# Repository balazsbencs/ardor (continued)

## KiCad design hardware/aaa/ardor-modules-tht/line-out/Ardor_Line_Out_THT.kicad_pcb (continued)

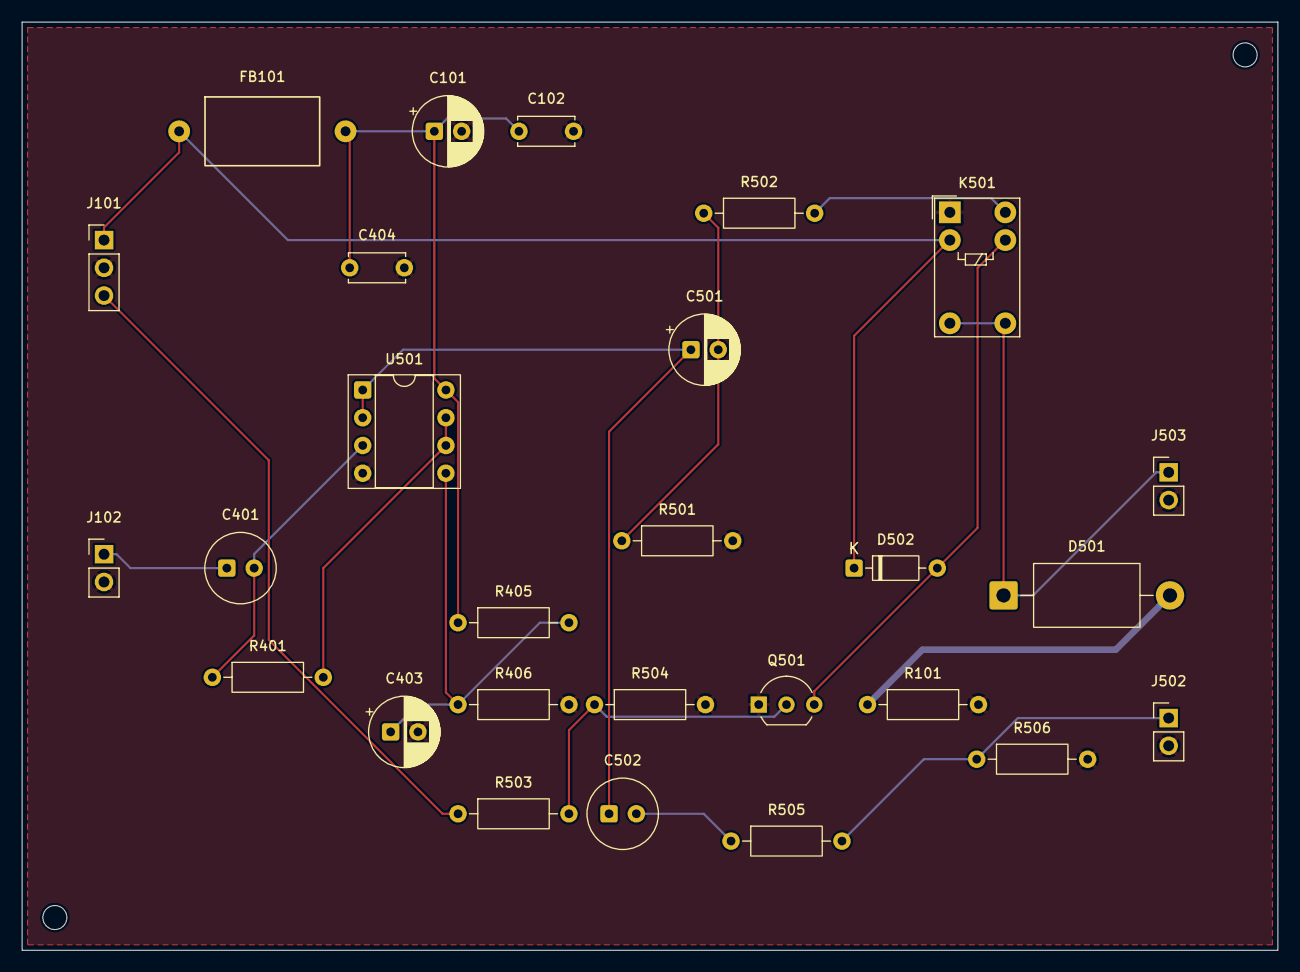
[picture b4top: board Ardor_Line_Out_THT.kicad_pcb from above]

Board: 2 copper layers, 115.0 x 85.0 mm, 29 parts (0 on the bottom side), 17 nets.

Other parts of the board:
H1, H2: MountingHole_2.2mm_M2

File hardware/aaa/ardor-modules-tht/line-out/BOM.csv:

Reference,Value,Footprint,Purchasing specification,Assembly
J102,MONO AUDIO INPUT FROM SOURCE,Connector_PinHeader_2.54mm:PinHeader_1x02_P2.54mm_Vertical,PinHeader_1x02_P2.54mm_Vertical,THT manual
J101,5V POWER + ENABLE INPUT,Connector_PinHeader_2.54mm:PinHeader_1x03_P2.54mm_Vertical,PinHeader_1x03_P2.54mm_Vertical,THT manual
J503,LINE AUDIO OUTPUT TO TS SOCKET,Connector_PinHeader_2.54mm:PinHeader_1x02_P2.54mm_Vertical,PinHeader_1x02_P2.54mm_Vertical,THT manual
J502,AUDIO OUTPUT TO AMP INPUT,Connector_PinHeader_2.54mm:PinHeader_1x02_P2.54mm_Vertical,PinHeader_1x02_P2.54mm_Vertical,THT manual
FB101,800R@100MHz / WE 7427501,Ardor_THT:Ferrite_WE_7427501_P15.24mm,Wurth Elektronik 7427501,THT manual
C101,22u / 25V polarized,Capacitor_THT:CP_Radial_D6.3mm_P2.50mm,"Radial electrolytic 22uF 25V, D<=6.3mm P2.5mm",THT manual
C102,100n / 50V X7R,Capacitor_THT:C_Disc_D5.0mm_W2.5mm_P5.00mm,"100nF 50V X7R radial, 5mm lead pitch",THT manual
C401,10u / 25V BIPOLAR,Ardor_THT:CP_Bipolar_D6.3mm_P2.50mm,Nichicon UES1E100MDM,THT manual
R401,100kR / 1% 0.25W,Resistor_THT:R_Axial_DIN0207_L6.3mm_D2.5mm_P10.16mm_Horizontal,Axial metal film 100kΩ 1% 0.25W,THT manual
U501,MCP6022-I/P,Package_DIP:DIP-8_W7.62mm_Socket,Microchip MCP6022-I/P,THT manual
C501,47u / 25V polarized,Capacitor_THT:CP_Radial_D6.3mm_P2.50mm,"Radial electrolytic 47uF 25V, D<=6.3mm P2.5mm",THT manual
R501,10kR / 1% 0.25W,Resistor_THT:R_Axial_DIN0207_L6.3mm_D2.5mm_P10.16mm_Horizontal,Axial metal film 10kΩ 1% 0.25W,THT manual
R502,100R / 1% 0.25W,Resistor_THT:R_Axial_DIN0207_L6.3mm_D2.5mm_P10.16mm_Horizontal,Axial metal film 100Ω 1% 0.25W,THT manual
K501,Omron G5V-1 DC5,Relay_THT:Relay_SPDT_Omron_G5V-1,Omron G5V-1 DC5,THT manual
D501,SA5.0CA-E3/54,Diode_THT:D_DO-15_P10.16mm_Horizontal,Vishay SA5.0CA-E3/54,THT manual
R101,0R / 1% 0.25W,Resistor_THT:R_Axial_DIN0207_L6.3mm_D2.5mm_P10.16mm_Horizontal,Axial metal film 0Ω 1% 0.25W,THT manual
Q501,2N3904 / E-B-C,Package_TO_SOT_THT:TO-92_Inline_Wide,onsemi 2N3904BU,THT manual
R503,470R / 1% 0.25W,Resistor_THT:R_Axial_DIN0207_L6.3mm_D2.5mm_P10.16mm_Horizontal,Axial metal film 470Ω 1% 0.25W,THT manual
R504,100kR / 1% 0.25W,Resistor_THT:R_Axial_DIN0207_L6.3mm_D2.5mm_P10.16mm_Horizontal,Axial metal film 100kΩ 1% 0.25W,THT manual
D502,1N4148,Diode_THT:D_DO-35_SOD27_P7.62mm_Horizontal,Vishay 1N4148-TAP,THT manual
R405,10kR / 1% 0.25W,Resistor_THT:R_Axial_DIN0207_L6.3mm_D2.5mm_P10.16mm_Horizontal,Axial metal film 10kΩ 1% 0.25W,THT manual
R406,10kR / 1% 0.25W,Resistor_THT:R_Axial_DIN0207_L6.3mm_D2.5mm_P10.16mm_Horizontal,Axial metal film 10kΩ 1% 0.25W,THT manual
C403,10u / 25V polarized,Capacitor_THT:CP_Radial_D6.3mm_P2.50mm,"Radial electrolytic 10uF 25V, D<=6.3mm P2.5mm",THT manual
C404,100n / 50V X7R,Capacitor_THT:C_Disc_D5.0mm_W2.5mm_P5.00mm,"100nF 50V X7R radial, 5mm lead pitch",THT manual
C502,10u / 25V BIPOLAR,Ardor_THT:CP_Bipolar_D6.3mm_P2.50mm,Nichicon UES1E100MDM,THT manual
R505,1kR / 1% 0.25W,Resistor_THT:R_Axial_DIN0207_L6.3mm_D2.5mm_P10.16mm_Horizontal,Axial metal film 1kΩ 1% 0.25W,THT manual
R506,100kR / 1% 0.25W,Resistor_THT:R_Axial_DIN0207_L6.3mm_D2.5mm_P10.16mm_Horizontal,Axial metal film 100kΩ 1% 0.25W,THT manual

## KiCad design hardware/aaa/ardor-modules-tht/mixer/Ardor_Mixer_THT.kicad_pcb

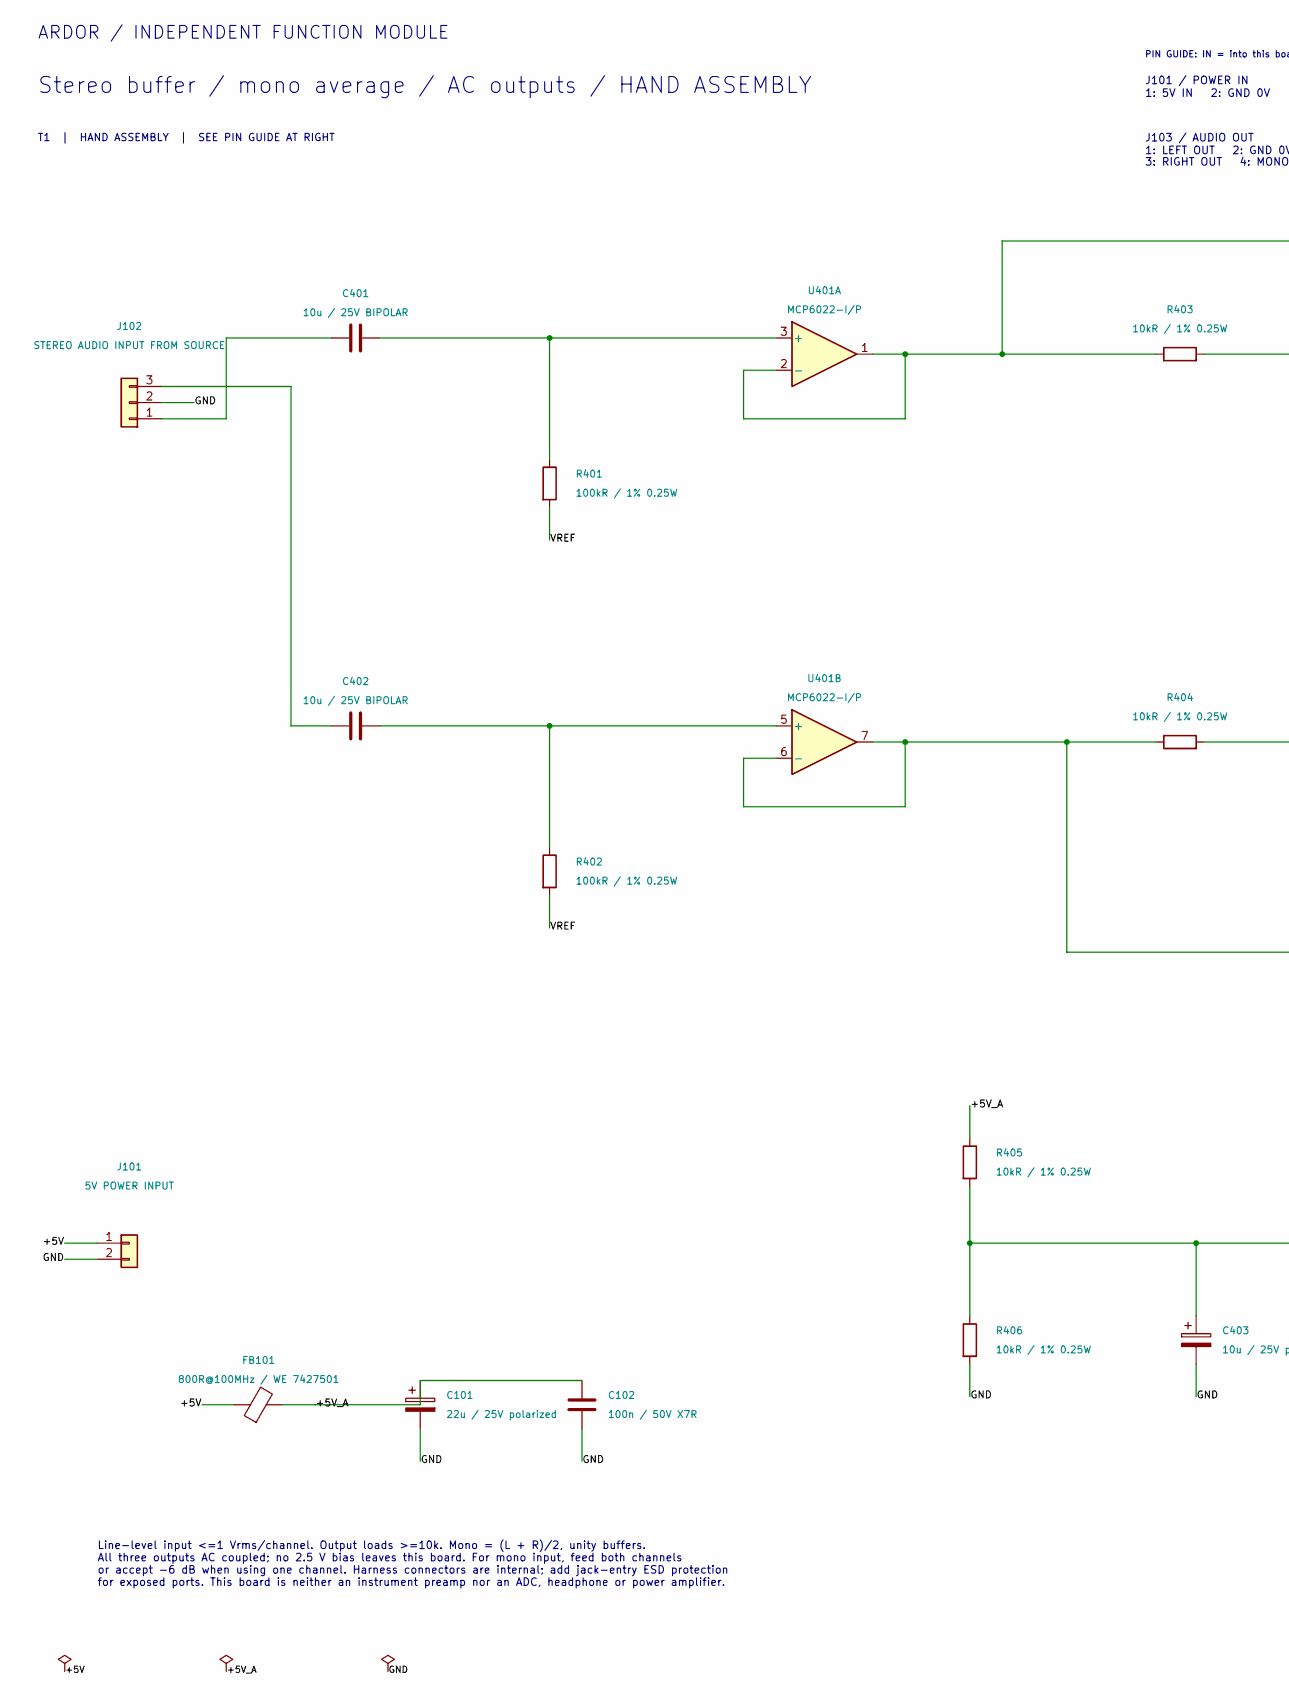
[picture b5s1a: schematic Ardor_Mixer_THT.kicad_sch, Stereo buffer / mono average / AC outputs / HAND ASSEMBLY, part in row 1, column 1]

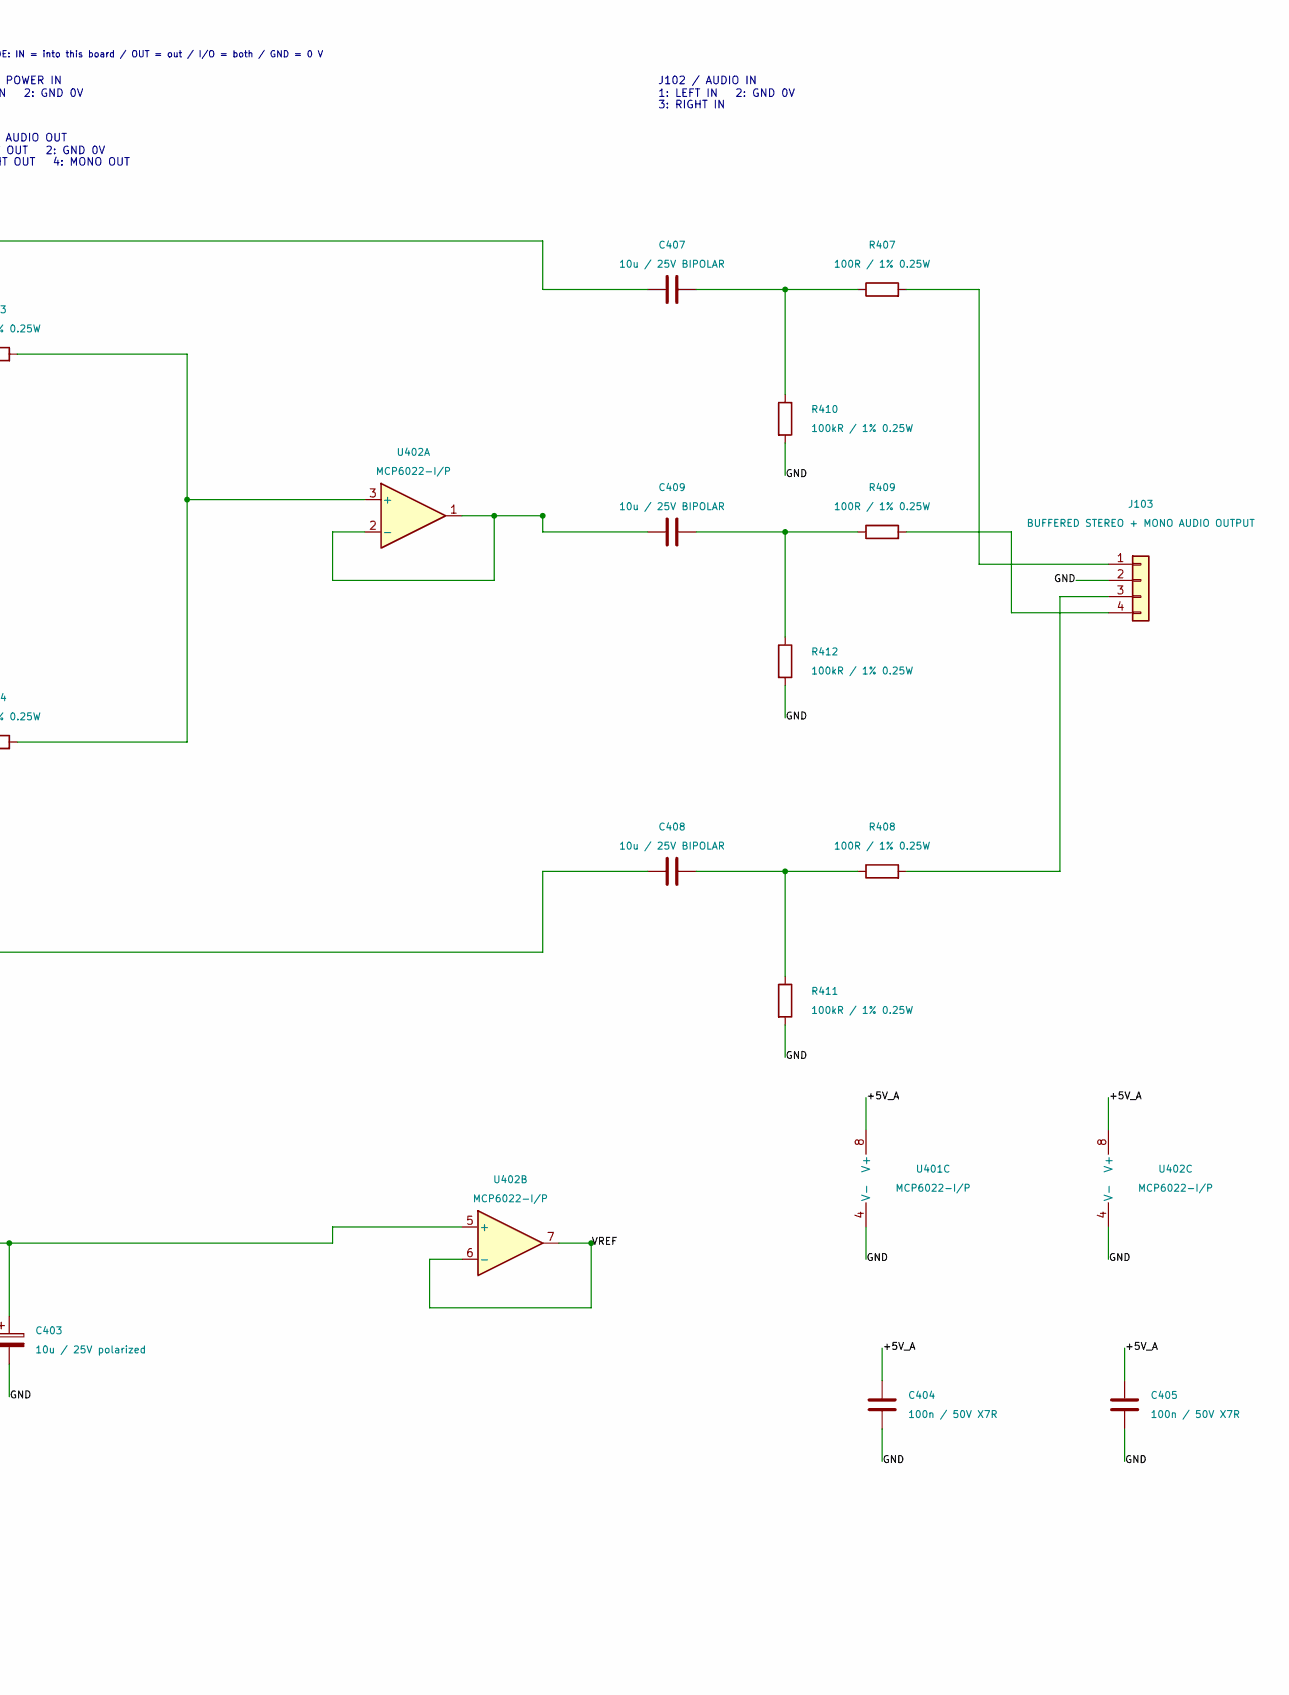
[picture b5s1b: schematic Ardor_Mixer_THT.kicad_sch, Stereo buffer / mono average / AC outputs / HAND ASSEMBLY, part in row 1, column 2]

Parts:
C101: 22u / 25V polarized; CP_Radial_D6.3mm_P2.50mm; MPN Radial electrolytic 22uF 25V, D<=6.3mm 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
C102, C404, C405: 100n / 50V X7R; C_Disc_D5.0mm_W2.5mm_P5.00mm; MPN 100nF 50V X7R radial, 5mm lead pitch
C401, C402, C407, C408, C409: 10u / 25V BIPOLAR; CP_Bipolar_D6.3mm_P2.50mm; MPN Nichicon UES1E100MDM
C403: 10u / 25V polarized; CP_Radial_D6.3mm_P2.50mm; MPN Radial electrolytic 10uF 25V, D<=6.3mm 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
FB101: 800R@100MHz / WE 7427501; Ferrite_WE_7427501_P15.24mm; MPN Wurth Elektronik 7427501
J101: 5V POWER INPUT; PinHeader_1x02_P2.54mm_Vertical; MPN PinHeader_1x02_P2.54mm_Vertical
J102: STEREO AUDIO INPUT FROM SOURCE; PinHeader_1x03_P2.54mm_Vertical; MPN PinHeader_1x03_P2.54mm_Vertical
J103: BUFFERED STEREO + MONO AUDIO OUTPUT; PinHeader_1x04_P2.54mm_Vertical; MPN PinHeader_1x04_P2.54mm_Vertical
R401, R402, R410, R411, R412: 100kR / 1% 0.25W; R_Axial_DIN0207_L6.3mm_D2.5mm_P10.16mm_Horizontal; MPN Axial metal film 100kΩ 1% 0.25W
R403, R404, R405, R406: 10kR / 1% 0.25W; R_Axial_DIN0207_L6.3mm_D2.5mm_P10.16mm_Horizontal; MPN Axial metal film 10kΩ 1% 0.25W
R407, R408, R409: 100R / 1% 0.25W; R_Axial_DIN0207_L6.3mm_D2.5mm_P10.16mm_Horizontal; MPN Axial metal film 100Ω 1% 0.25W
U401, U402: MCP6022-I/P; DIP-8_W7.62mm_Socket; MPN Microchip MCP6022-I/P

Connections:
/+5V: FB101.1, J101.1
/+5V_A: C101.1, C102.1, C404.1, C405.1, FB101.2, R405.1, U401.8 (V+), U402.8 (V+)
/GND: C101.2, C102.2, C403.2, C404.2, C405.2, J101.2, J102.2, J103.2, R406.2, R410.2, R411.2, R412.2, U401.4 (V-), U402.4 (V-)
/VREF: R401.2, R402.2, U402.6 (-), U402.7
unnamed: C407.2, R407.1, R410.1
unnamed: C408.2, R408.1, R411.1
unnamed: C409.2, R409.1, R412.1
unnamed: C401.1, J102.1
unnamed: C402.1, J102.3
unnamed: J103.1, R407.2
unnamed: J103.3, R408.2
unnamed: J103.4, R409.2
unnamed: C401.2, R401.1, U401.3 (+)
unnamed: C407.1, R403.1, U401.1, U401.2 (-)
unnamed: C402.2, R402.1, U401.5 (+)
unnamed: C408.1, R404.1, U401.6 (-), U401.7
unnamed: R403.2, R404.2, U402.3 (+)
unnamed: C409.1, U402.1, U402.2 (-)
unnamed: C403.1, R405.2, R406.1, U402.5 (+)

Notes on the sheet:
ARDOR / INDEPENDENT FUNCTION MODULE
Stereo buffer / mono average / AC outputs / HAND ASSEMBLY
T1 | HAND ASSEMBLY | SEE PIN GUIDE AT RIGHT
Line-level input <=1 Vrms/channel. Output loads >=10k. Mono = (L + R)/2, unity buffers. All three outputs AC coupled; no 2.5 V bias leaves this board. For mono input, feed both channels or accept -6 dB when using one channel. Harness connectors are internal; add jack-entry ESD protection for expose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
PIN GUIDE: IN = into this board / OUT = out / I/O = both / GND = 0 V
J101 / POWER IN
1: 5V IN 2: GND 0V
J102 / AUDIO IN
1: LEFT IN 2: GND 0V
3: RIGHT IN
J103 / AUDIO OUT
1: LEFT OUT 2: GND 0V
3: RIGHT OUT 4: MONO OUT

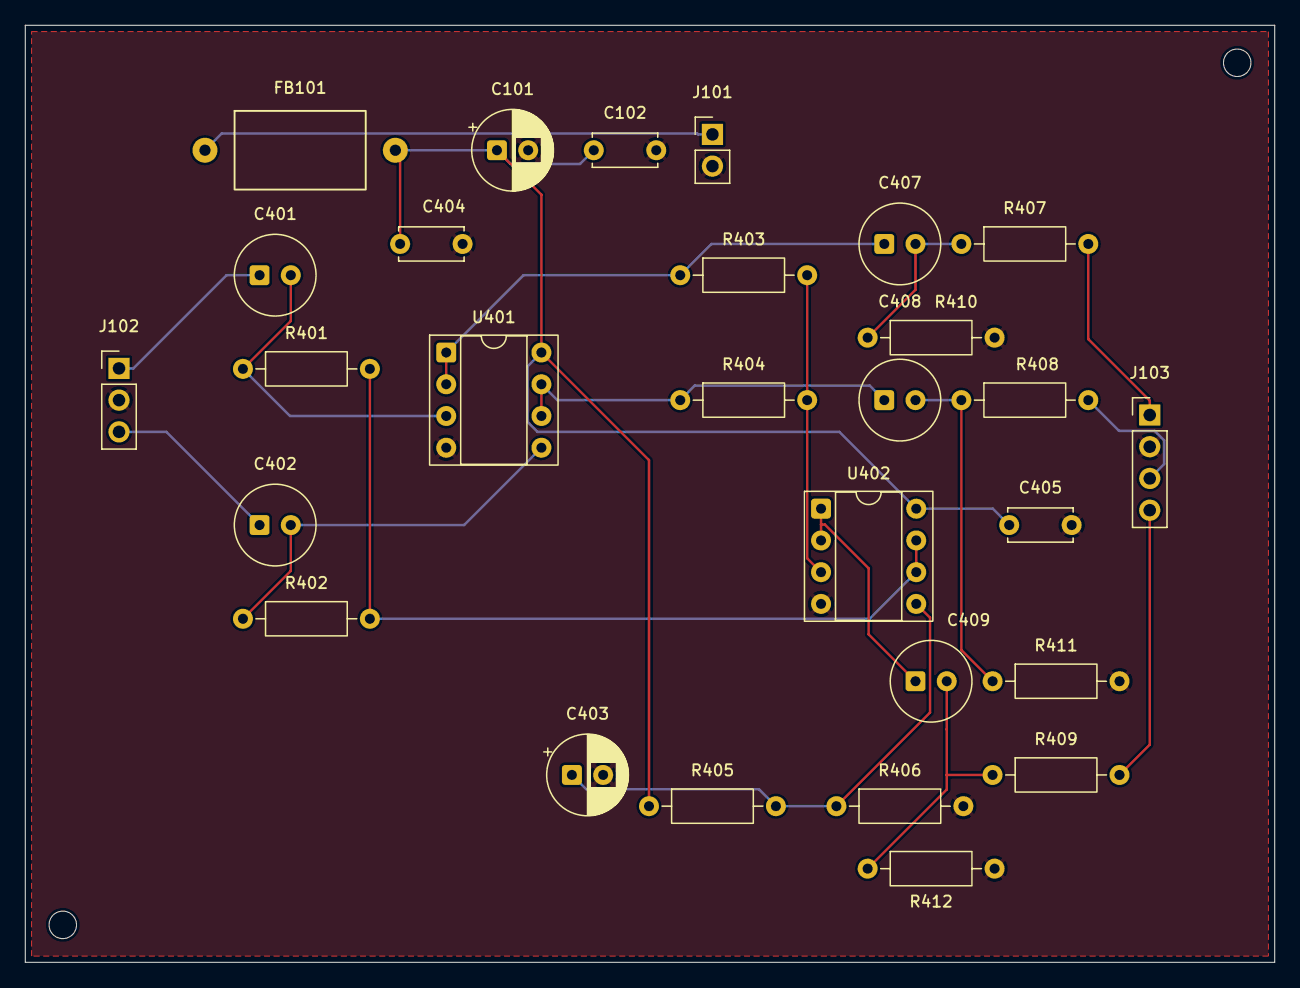
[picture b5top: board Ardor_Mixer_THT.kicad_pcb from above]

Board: 2 copper layers, 100.0 x 75.0 mm, 30 parts (0 on the bottom side), 19 nets.

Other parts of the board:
H1, H2: MountingHole_2.2mm_M2

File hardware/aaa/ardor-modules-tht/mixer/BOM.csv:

Reference,Value,Footprint,Purchasing specification,Assembly
J102,STEREO AUDIO INPUT FROM SOURCE,Connector_PinHeader_2.54mm:PinHeader_1x03_P2.54mm_Vertical,PinHeader_1x03_P2.54mm_Vertical,THT manual
J101,5V POWER INPUT,Connector_PinHeader_2.54mm:PinHeader_1x02_P2.54mm_Vertical,PinHeader_1x02_P2.54mm_Vertical,THT manual
J103,"BUFFERED STEREO + MONO AUDIO
OUTPUT",Connector_PinHeader_2.54mm:PinHeader_1x04_P2.54mm_Vertical,PinHeader_1x04_P2.54mm_Vertical,THT manual
FB101,800R@100MHz / WE 7427501,Ardor_THT:Ferrite_WE_7427501_P15.24mm,Wurth Elektronik 7427501,THT manual
C101,22u / 25V polarized,Capacitor_THT:CP_Radial_D6.3mm_P2.50mm,"Radial electrolytic 22uF 25V, D<=6.3mm P2.5mm",THT manual
C102,100n / 50V X7R,Capacitor_THT:C_Disc_D5.0mm_W2.5mm_P5.00mm,"100nF 50V X7R radial, 5mm lead pitch",THT manual
C401,10u / 25V BIPOLAR,Ardor_THT:CP_Bipolar_D6.3mm_P2.50mm,Nichicon UES1E100MDM,THT manual
R401,100kR / 1% 0.25W,Resistor_THT:R_Axial_DIN0207_L6.3mm_D2.5mm_P10.16mm_Horizontal,Axial metal film 100kΩ 1% 0.25W,THT manual
U401,MCP6022-I/P,Package_DIP:DIP-8_W7.62mm_Socket,Microchip MCP6022-I/P,THT manual
R403,10kR / 1% 0.25W,Resistor_THT:R_Axial_DIN0207_L6.3mm_D2.5mm_P10.16mm_Horizontal,Axial metal film 10kΩ 1% 0.25W,THT manual
C402,10u / 25V BIPOLAR,Ardor_THT:CP_Bipolar_D6.3mm_P2.50mm,Nichicon UES1E100MDM,THT manual
R402,100kR / 1% 0.25W,Resistor_THT:R_Axial_DIN0207_L6.3mm_D2.5mm_P10.16mm_Horizontal,Axial metal film 100kΩ 1% 0.25W,THT manual
R404,10kR / 1% 0.25W,Resistor_THT:R_Axial_DIN0207_L6.3mm_D2.5mm_P10.16mm_Horizontal,Axial metal film 10kΩ 1% 0.25W,THT manual
U402,MCP6022-I/P,Package_DIP:DIP-8_W7.62mm_Socket,Microchip MCP6022-I/P,THT manual
C407,10u / 25V BIPOLAR,Ardor_THT:CP_Bipolar_D6.3mm_P2.50mm,Nichicon UES1E100MDM,THT manual
R407,100R / 1% 0.25W,Resistor_THT:R_Axial_DIN0207_L6.3mm_D2.5mm_P10.16mm_Horizontal,Axial metal film 100Ω 1% 0.25W,THT manual
R410,100kR / 1% 0.25W,Resistor_THT:R_Axial_DIN0207_L6.3mm_D2.5mm_P10.16mm_Horizontal,Axial metal film 100kΩ 1% 0.25W,THT manual
C408,10u / 25V BIPOLAR,Ardor_THT:CP_Bipolar_D6.3mm_P2.50mm,Nichicon UES1E100MDM,THT manual
R408,100R / 1% 0.25W,Resistor_THT:R_Axial_DIN0207_L6.3mm_D2.5mm_P10.16mm_Horizontal,Axial metal film 100Ω 1% 0.25W,THT manual
R411,100kR / 1% 0.25W,Resistor_THT:R_Axial_DIN0207_L6.3mm_D2.5mm_P10.16mm_Horizontal,Axial metal film 100kΩ 1% 0.25W,THT manual
C409,10u / 25V BIPOLAR,Ardor_THT:CP_Bipolar_D6.3mm_P2.50mm,Nichicon UES1E100MDM,THT manual
R409,100R / 1% 0.25W,Resistor_THT:R_Axial_DIN0207_L6.3mm_D2.5mm_P10.16mm_Horizontal,Axial metal film 100Ω 1% 0.25W,THT manual
R412,100kR / 1% 0.25W,Resistor_THT:R_Axial_DIN0207_L6.3mm_D2.5mm_P10.16mm_Horizontal,Axial metal film 100kΩ 1% 0.25W,THT manual
R405,10kR / 1% 0.25W,Resistor_THT:R_Axial_DIN0207_L6.3mm_D2.5mm_P10.16mm_Horizontal,Axial metal film 10kΩ 1% 0.25W,THT manual
R406,10kR / 1% 0.25W,Resistor_THT:R_Axial_DIN0207_L6.3mm_D2.5mm_P10.16mm_Horizontal,Axial metal film 10kΩ 1% 0.25W,THT manual
C403,10u / 25V polarized,Capacitor_THT:CP_Radial_D6.3mm_P2.50mm,"Radial electrolytic 10uF 25V, D<=6.3mm P2.5mm",THT manual
C404,100n / 50V X7R,Capacitor_THT:C_Disc_D5.0mm_W2.5mm_P5.00mm,"100nF 50V X7R radial, 5mm lead pitch",THT manual
C405,100n / 50V X7R,Capacitor_THT:C_Disc_D5.0mm_W2.5mm_P5.00mm,"100nF 50V X7R radial, 5mm lead pitch",THT manual

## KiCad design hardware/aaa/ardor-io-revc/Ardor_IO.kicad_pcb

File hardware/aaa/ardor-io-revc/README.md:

# Ardor IO — Rev C, budget SMT

Rev C is an alternate 68 × 46 mm, two-layer board for two-board JLCPCB SMT assembly. It retains DIN MIDI input, passive expression input, mono line output with startup relay mute, and the internal amp feed. Headphones are omitted. The full-featured revision remains in [../ardor-io](../ardor-io/README.md).

Open `Ardor_IO.kicad_pro` in KiCad 9. Use the [connected one-page schematic](review/Ardor_IO_connected.pdf) to follow the circuit, or [Ardor_IO.pdf](Ardor_IO.pdf) for the five editable schematic sheets. The [assembly guide](assembly/README.md) contains the Gerber ZIP, exact JLCPCB BOM, CPL and placement reference.

| For two assembled boards | Previous revision | Rev C |
| --- | ---: | ---: |
| SMT placements per board | 76 | 60 |
| Unique SMT parts | 28 | 24 |
| Extended part types | 15 | 8 |
| Modelled components, including minimums/loss | $39.06 | $16.57 |
| Economic feeder fees at $3.07/type | $46.05 | $24.56 |
| Components + feeder subtotal | $85.11 | $41.13 |

This model predicts **$43.98 less for two boards** in components and feeder fees. It is not a checkout quotation or a guaranteed total. PCB fabrication, setup, stencil, joints, shipping, tax, fixtures, manual parts and discounts are outside the subtotal. The earlier user quote was $108 for two assembled boards; its fee breakdown was not provided. See [cost-comparison.json](assembly/cost-comparison.json), the dated inventory snapshots and [JLCPCB's current price schedule](https://jlcpcb.com/help/article/pcb-assembly-price). Rev C also removes the headphone QFN and its X-ray inspection requirement.

## Changes and tradeoffs

- Two TI TLV9002IDR SOIC-8 dual op-amps replace three OPA2320 devices. The mono buffer feeds two separate coupling capacitors and source resistors. The line and amp outputs share this buffer; simultaneous loads must meet the specified minimum impedances.
- ADS1115, address 0x48, GPIO mapping, pedal polarity selector, H11L1M optocoupler, relay driver and jack protection remain. Firmware can keep the existing MIDI, expression and line-mute interfaces. GPIO17 is unused.
- Mono averaging resistors are 10 kΩ / 1%, shared with other Basic resistors. Worst-case weights are 0.495 and 0.505; opposite-phase inputs can leave a 1% residual, instead of the previous 0.1% resistor target.
- Supply bulk and audio coupling capacitors use Basic Samsung X5R parts. The 50 V, 1206 audio capacitors retain their nominal 10 µF. X5R has a lower temperature limit than X7R and still has voltage-dependent capacitance, microphonics and distortion that require measurement.
- The three 0603 ferrites are Basic Murata BLM18PG121SN1D, 120 Ω at 100 MHz rather than 600 Ω. DC operation is retained; RF attenuation changes. No assembled-enclosure EMC claim is made.
- The outline and mounting coordinates match the compact board. Removed circuitry leaves spare area; enclosure fit, Pi stack height and panel-jack choices still need mechanical confirmation.
- Ground uses the filled front/back copper: 192 redundant GND track segments (324.13 mm) are removed. Three short local links and all 20 ground vias remain. See the [before/after routing view](routing/ground-routing.svg) and [ground audit](verification/ground-routing-audit.json). CHASSIS and signal routing are unchanged. A smaller outline would require moving components and mounting holes; removing tracks alone does not create that mechanical clearance.
- Both 3.3 V rails use uniform 0.20 mm tracks. Their low current makes wider runs unnecessary; the [width audit](verification/3v3-width-audit.json) checks every segment and a conservative track-resistance estimate. All other track widths and all route centerlines retain the reviewed layout.

The board passes all-severity ERC and DRC, with zero unconnected or parity findings and no exclusions. [Connectivity audit](verification/connectivity-audit.json) checks all **219 electrical pad/net assignments** and 199 intended non-NC connections. The one-page drawing separately checks coverage of all 80 components and wire geometry. This is an engineering prototype; audio, hot-plug, startup and enclosure tests have not been performed.

Read [DESIGN_NOTES.md](DESIGN_NOTES.md) before building. SMT is assembled by JLCPCB; headers, optocoupler, relay, panel connectors and shunts are fitted by hand.

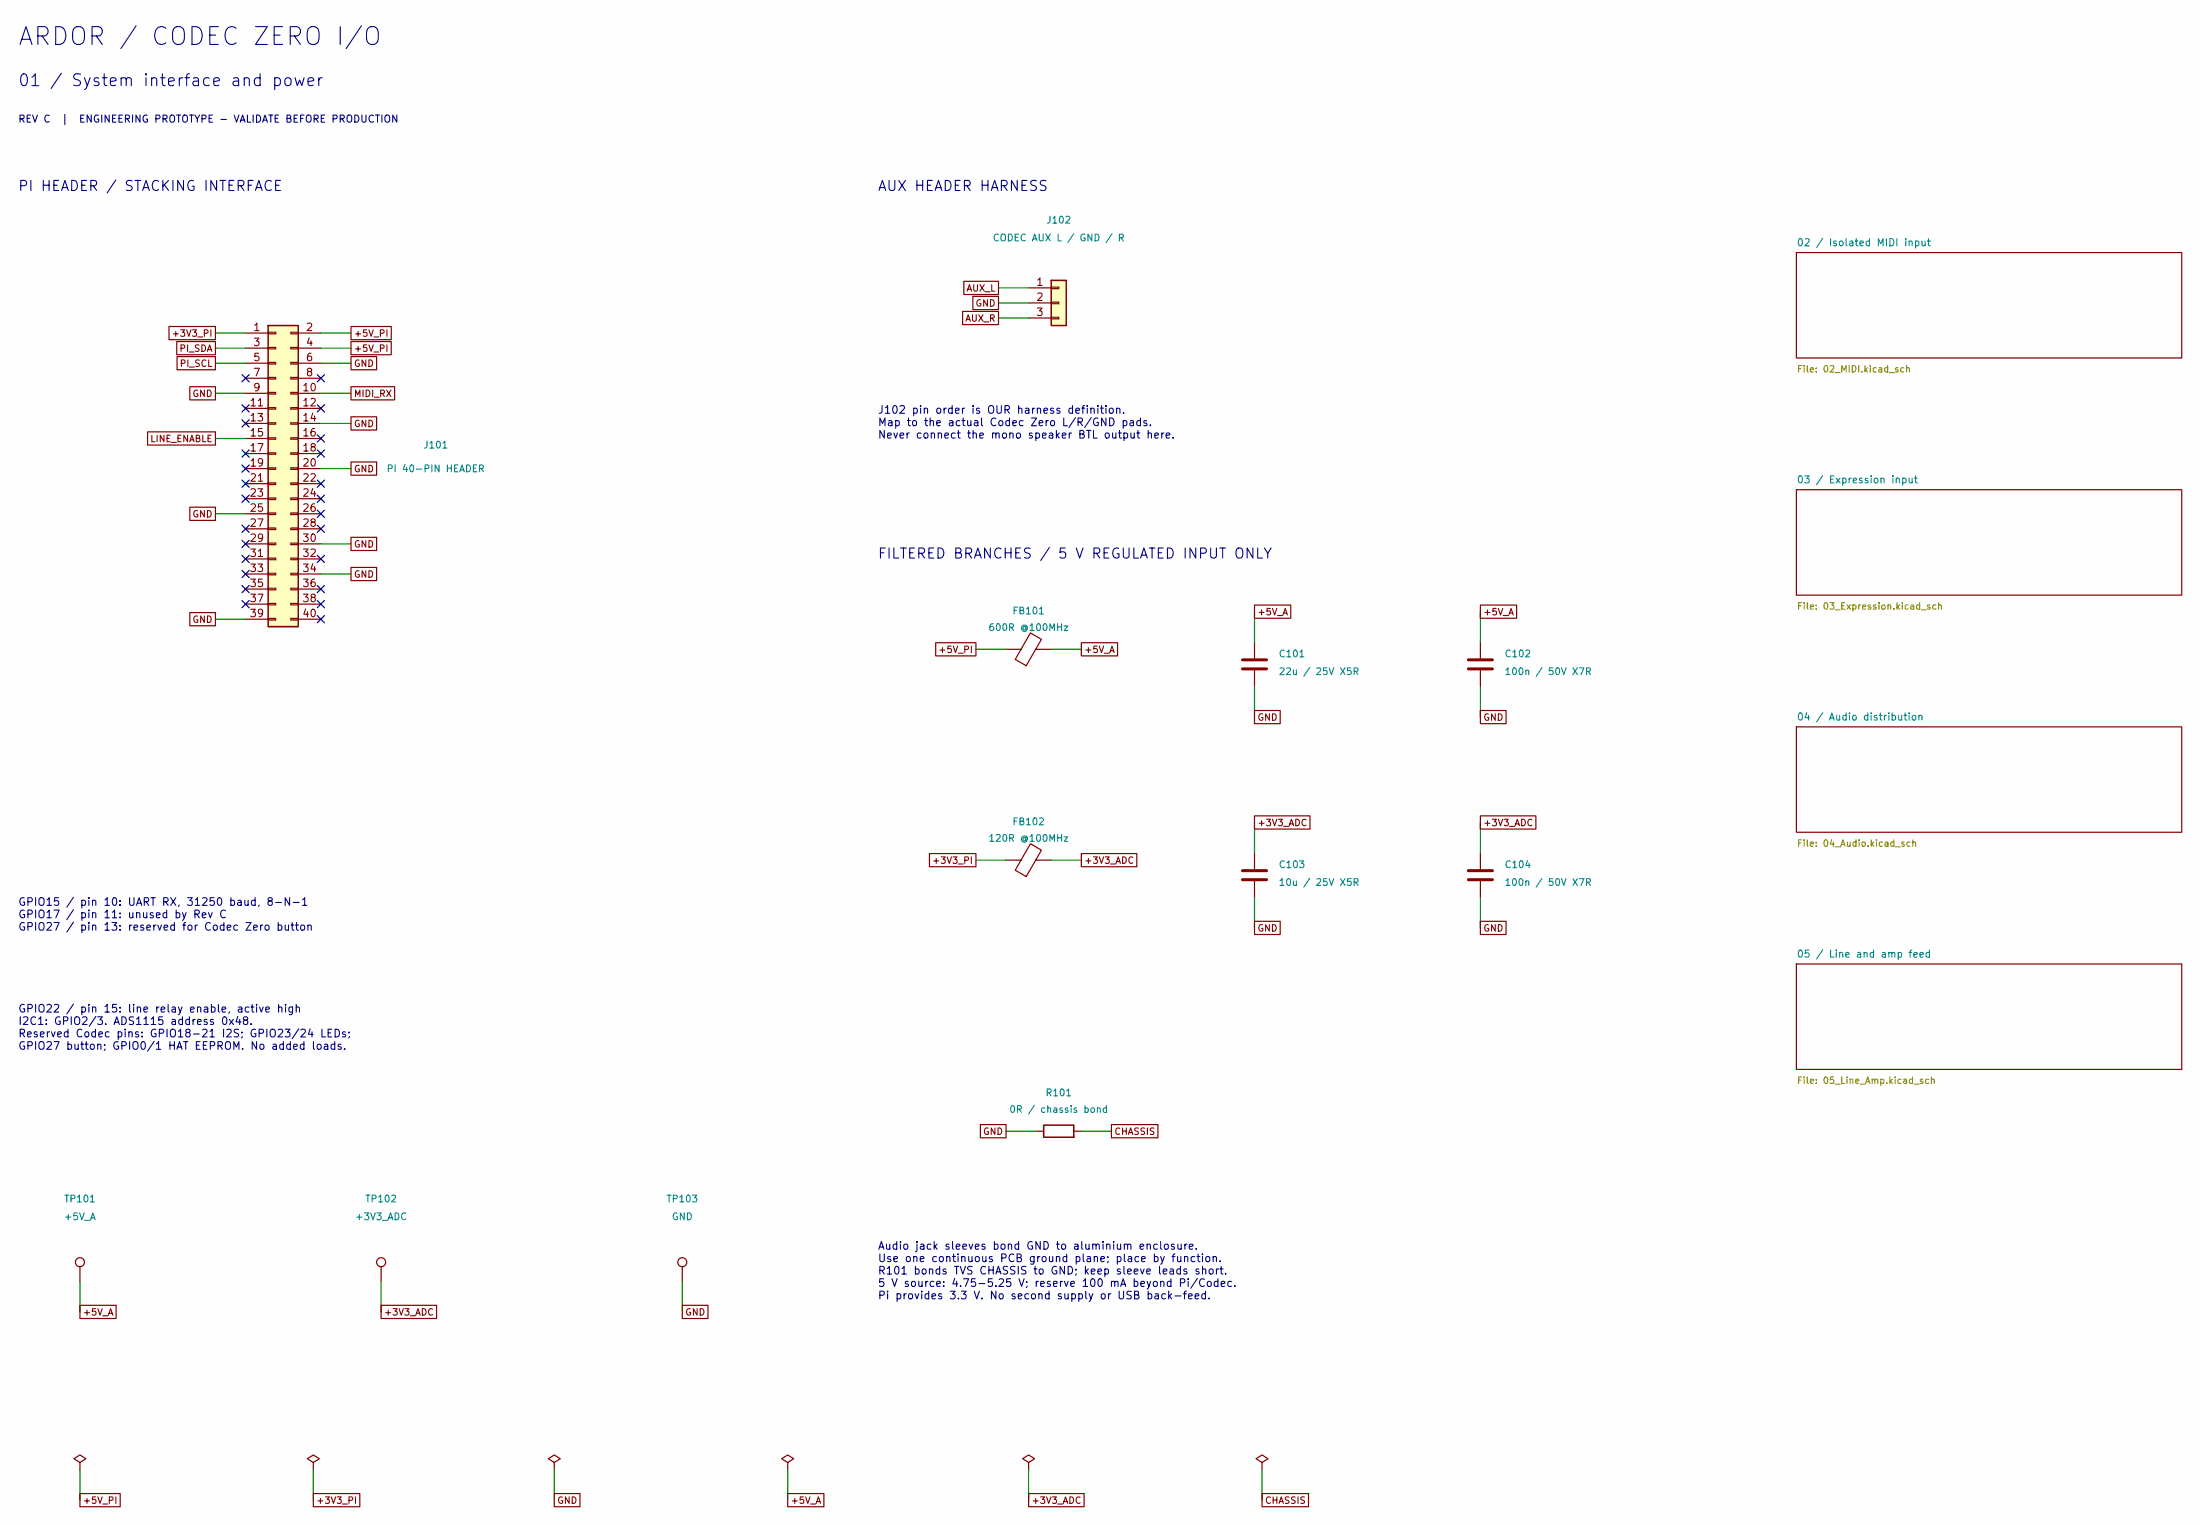
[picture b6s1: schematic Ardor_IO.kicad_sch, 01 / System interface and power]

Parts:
C101: 22u / 25V X5R; C_0805_2012Metric; MPN Samsung Electro-Mechanics CL21A226MAQNN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; JLCPCB Part # C45783
C102, C104: 100n / 50V X7R; C_0603_1608Metric; MPN YAGEO CC0603KRX7R9BB104; JLCPCB Part # C14663
C103: 10u / 25V X5R; C_0805_2012Metric; MPN Samsung Electro-Mechanics CL21A106KAYNN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; JLCPCB Part # C15850
FB101: 600R @100MHz; L_0805_2012Metric; MPN Murata BLM21PG601SN1D; JLCPCB Part # C41556732
FB102: 120R @100MHz; R_0603_1608Metric; MPN Murata Electronics BLM18PG121SN1D; JLCPCB Part # C14709
J101: PI 40-PIN HEADER; PinSocket_2x20_P2.54mm_Vertical; MPN Samtec SSQ-120-03-G-D (verify stack hei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
J102: CODEC AUX L / GND / R; PinHeader_1x03_P2.54mm_Vertical
R101: 0R / chassis bond; R_1206_3216Metric; MPN UNI-ROYAL 1206W4F0000T5E; JLCPCB Part # C17888
TP101: +5V_A; TestPoint_Pad_D1.5mm
TP102: +3V3_ADC; TestPoint_Pad_D1.5mm
TP103: GND; TestPoint_Pad_D1.5mm

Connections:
+3V3_ADC: C103.1, C104.1, FB102.2, TP102.1; also elsewhere on the board
+3V3_PI: FB102.1, J101.1; also elsewhere on the board
+5V_A: C101.1, C102.1, FB101.2, TP101.1; also elsewhere on the board
+5V_PI: FB101.1, J101.2, J101.4; also elsewhere on the board
AUX_L: J102.1; also elsewhere on the board
AUX_R: J102.3; also elsewhere on the board
CHASSIS: R101.2; also elsewhere on the board
GND: C101.2, C102.2, C103.2, C104.2, J101.6, J101.9, J101.14, J101.20, J101.25, J101.30, J101.34, J101.39, J102.2, R101.1, TP103.1; also elsewhere on the board
LINE_ENABLE: J101.15; also elsewhere on the board
MIDI_RX: J101.10; also elsewhere on the board
PI_SCL: J101.5; also elsewhere on the board
PI_SDA: J101.3; also elsewhere on the board

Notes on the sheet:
ARDOR / CODEC ZERO I/O
01 / System interface and power
REV C | ENGINEERING PROTOTYPE - VALIDATE BEFORE PRODUCTION
PI HEADER / STACKING INTERFACE
GPIO15 / pin 10: UART RX, 31250 baud, 8-N-1 GPIO17 / pin 11: unused by Rev C GPIO27 / pin 13: reserved for Codec Zero button
GPIO22 / pin 15: line relay enable, active high I2C1: GPIO2/3. ADS1115 address 0x48. Reserved Codec pins: GPIO18-21 I2S; GPIO23/24 LEDs; GPIO27 button; GPIO0/1 HAT EEPROM. No added loads.
AUX HEADER HARNESS
J102 pin order is OUR harness definition. Map to the actual Codec Zero L/R/GND pads. Never connect the mono speaker BTL output here.
FILTERED BRANCHES / 5 V REGULATED INPUT ONLY
Audio jack sleeves bond GND to aluminium enclosure. Use one continuous PCB ground plane; place by function. R101 bonds TVS CHASSIS to GND; keep sleeve leads short. 5 V source: 4.75-5.25 V; reserve 100 mA beyond Pi/Codec. Pi provides 3.3 V. No second supply or USB back-feed.

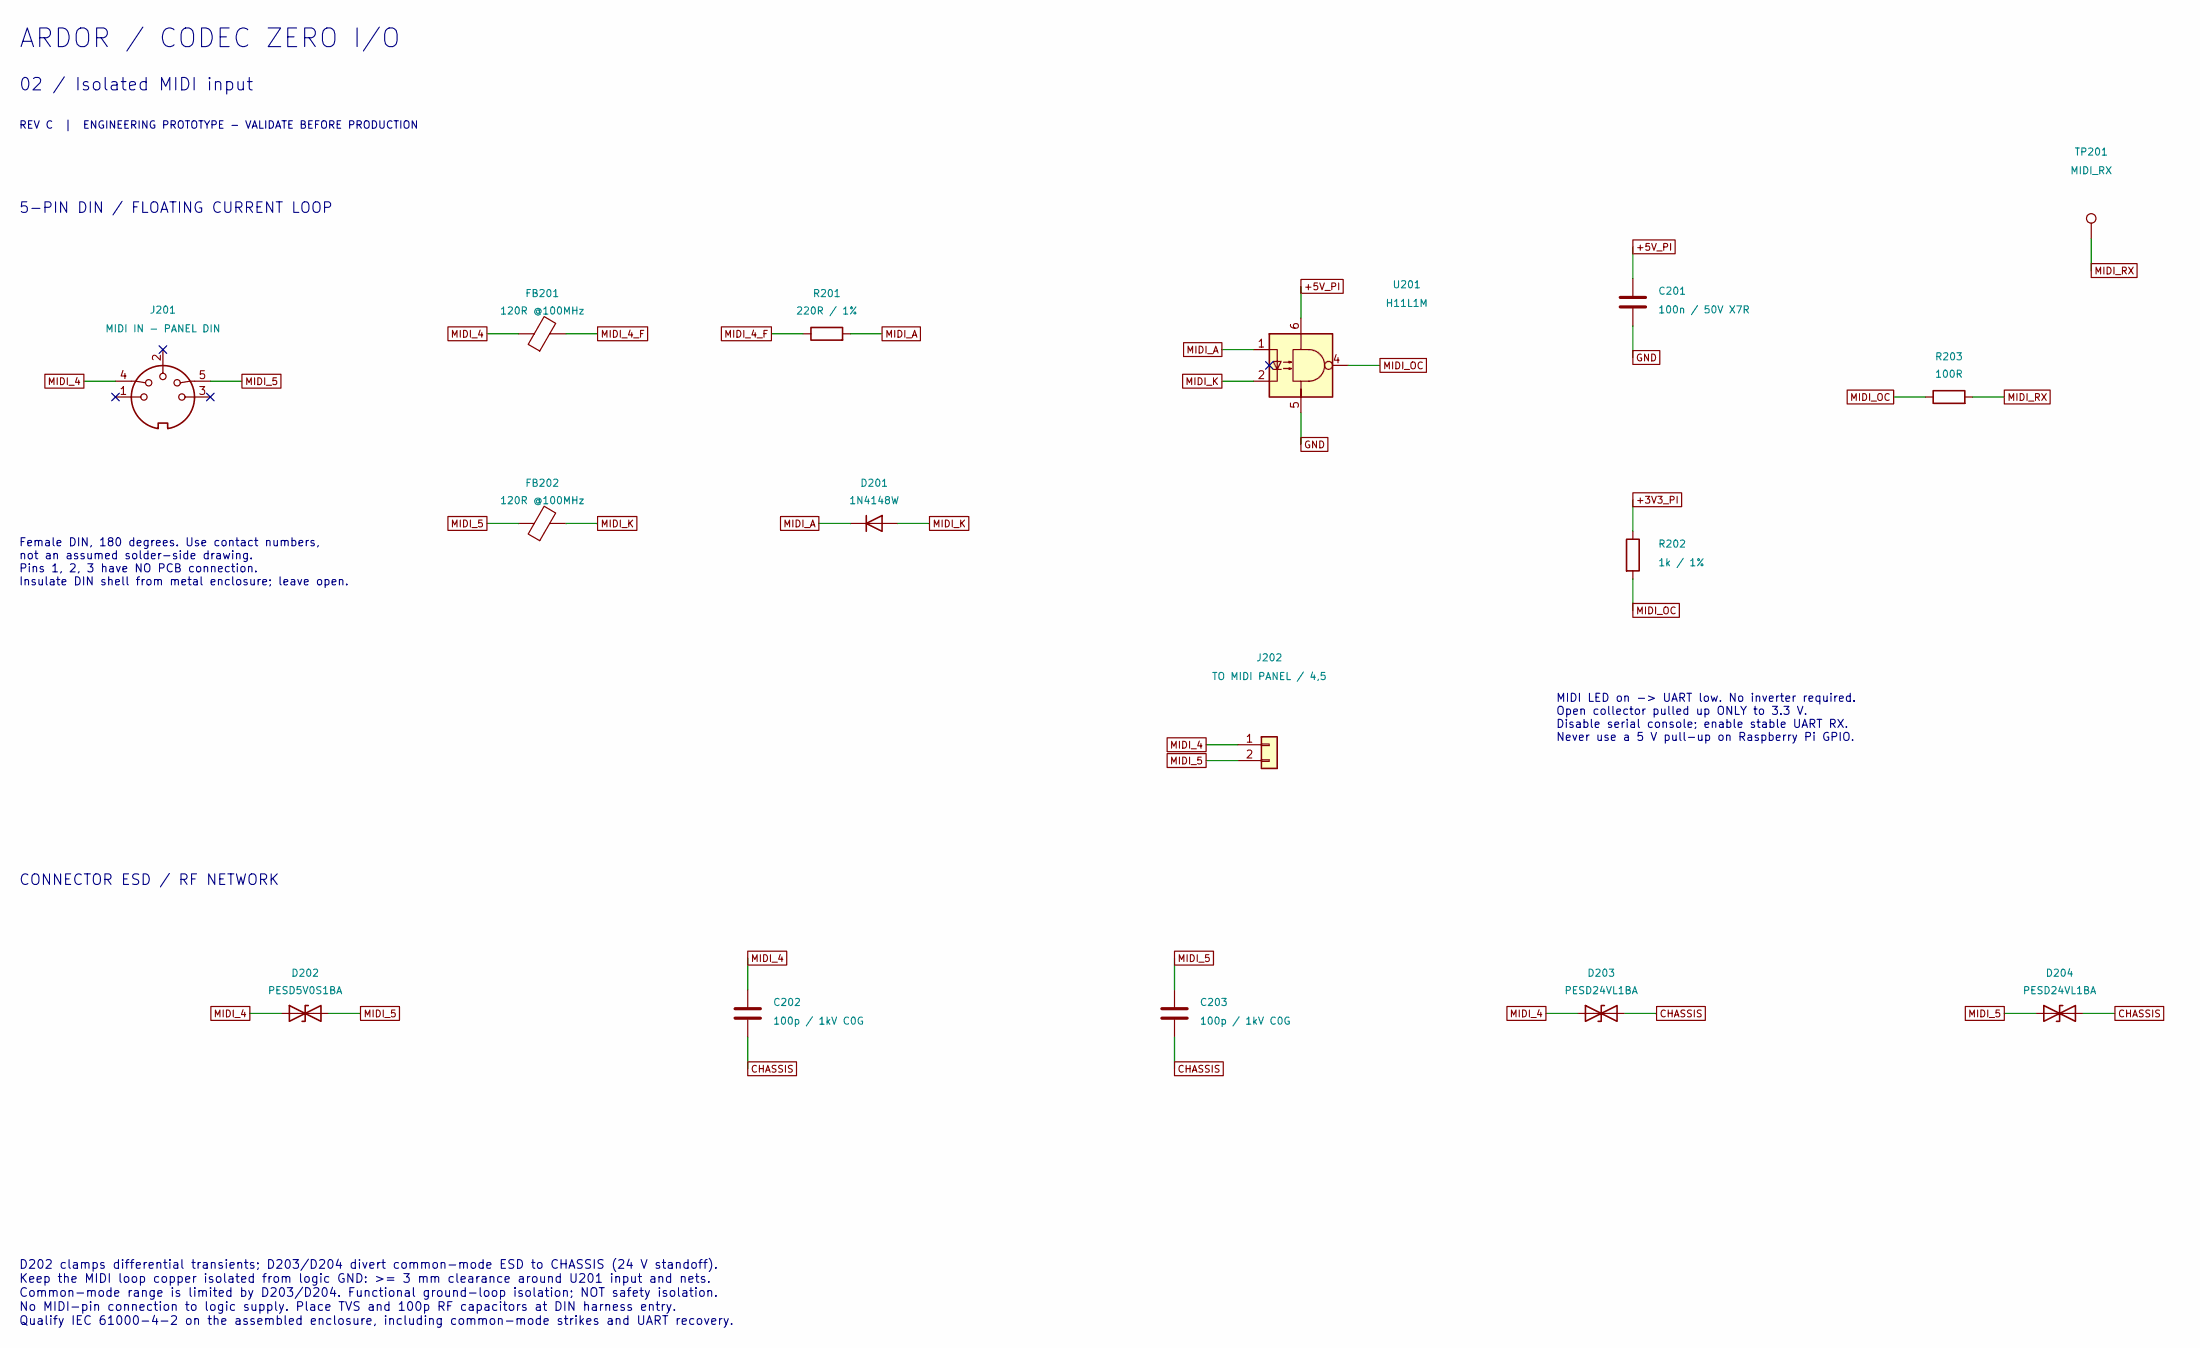
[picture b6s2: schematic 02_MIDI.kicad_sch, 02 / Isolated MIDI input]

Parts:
C201: 100n / 50V X7R; C_0603_1608Metric; MPN YAGEO CC0603KRX7R9BB104; JLCPCB Part # C14663
C202, C203: 100p / 1kV C0G; C_1206_3216Metric; MPN CCTC TCC1206COG101J102DT; JLCPCB Part # C367316
D201: 1N4148W; D_SOD-123; MPN ST(Semtech) 1N4148W; JLCPCB Part # C81598
D202: PESD5V0S1BA; D_SOD-323; MPN Nexperia PESD5V0S1BA,115; JLCPCB Part # C19224
D203, D204: PESD24VL1BA; D_SOD-323; MPN Nexperia PESD24VL1BA,115; JLCPCB Part # C69324
FB201, FB202: 120R @100MHz; R_0603_1608Metric; MPN Murata Electronics BLM18PG121SN1D; JLCPCB Part # C14709
J201: MIDI IN - PANEL DIN
J202: TO MIDI PANEL / 4,5; PinHeader_1x02_P2.54mm_Vertical
R201: 220R / 1%; R_0603_1608Metric; MPN UNI-ROYAL 0603WAF2200T5E; JLCPCB Part # C22962
R202: 1k / 1%; R_0603_1608Metric; MPN UNI-ROYAL 0603WAF1001T5E; JLCPCB Part # C21190
R203: 100R; R_0603_1608Metric; MPN UNI-ROYAL 0603WAF1000T5E; JLCPCB Part # C22775
TP201: MIDI_RX; TestPoint_Pad_D1.5mm
U201: H11L1M; DIP-6_W7.62mm; MPN onsemi H11L1M

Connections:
+3V3_PI: R202.1; also elsewhere on the board
+5V_PI: C201.1, U201.6; also elsewhere on the board
CHASSIS: C202.2, C203.2, D203.2 (A2), D204.2 (A2); also elsewhere on the board
GND: C201.2, U201.5; also elsewhere on the board
MIDI_4: C202.1, D202.1 (A1), D203.1 (A1), FB201.1, J201.4, J202.1
MIDI_4_F: FB201.2, R201.1
MIDI_5: C203.1, D202.2 (A2), D204.1 (A1), FB202.1, J201.5, J202.2
MIDI_A: D201.1 (K), R201.2, U201.1
MIDI_K: D201.2 (A), FB202.2, U201.2
MIDI_OC: R202.2, R203.1, U201.4
MIDI_RX: R203.2, TP201.1; also elsewhere on the board

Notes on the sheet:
ARDOR / CODEC ZERO I/O
02 / Isolated MIDI input
REV C | ENGINEERING PROTOTYPE - VALIDATE BEFORE PRODUCTION
5-PIN DIN / FLOATING CURRENT LOOP
Female DIN, 180 degrees. Use contact numbers, not an assumed solder-side drawing. Pins 1, 2, 3 have NO PCB connection. Insulate DIN shell from metal enclosure; leave open.
MIDI LED on -> UART low. No inverter required. Open collector pulled up ONLY to 3.3 V. Disable serial console; enable stable UART RX. Never use a 5 V pull-up on Raspberry Pi GPIO.
CONNECTOR ESD / RF NETWORK
D202 clamps differential transients; D203/D204 divert common-mode ESD to CHASSIS (24 V standoff). Keep the MIDI loop copper isolated from logic GND: >= 3 mm clearance around U201 input and nets. Common-mode range is limited by D203/D204. Functional ground-loop isolation; NOT safety isolation. No MI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
